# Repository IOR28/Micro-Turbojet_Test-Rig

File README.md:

# Micro-Turbojet Test Rig

This repository contains all the files created during my thesis, Test Rig Design for a Micro-Turbojet Engine. More information about these contents, designs and uses can be found in the document of the thesis.

Different parts of the test rig design where explored during the project, these are sepparated into folders with the same topic. The explanation of this organization and a brief explanation of each subproject can be found below.

### Contents

+ [StructureDesign](#structuredesign): Autodesk Inventor project
	+ Bellmouth: Parts, drawings and final files
	+ CommercialParts
	+ DesignedParts: Parts and drawings
+ [DataAcquisitionMCs](#dataacquisitionmcs): MPLAB X projects
	+ Pressure
	+ Temperature
	+ Thrust_Flow
+ [DataProcessingMaster](#dataprocessingmaster): Python files and classes
+ [PCBDesigns](#pcbdesigns): Autodesk Eagle projects
	+ RTD_conditioning
	+ System_control
	+ General_board

## [StructureDesign](./StructureDesign)

This folder contains the Autodesk Inventor files of the designed bench. the bench features both [commercial parts](./StructureDesign/CommercialParts) and [designed parts](./StructureDesign/DesignedParts). The design of a [bellmouth](./StructureDesign/Bellmouth) is also included.

All the designed components have their corresponding sketches in DWG, DXF and PDF formats so that they can be manufactured. The bellmouth is expected to be 3D printed, therefore, STL files are profided along with the sketches. The links to the commercial parts can be found in the budget of the project (document).

## [DataAcquisitionMCs](./DataAcquisitionMCs)

Here the MPLAB X projects can be found. Files are coded in C and are divided into 3 projects (each one corresponding to a microcontroller):
+ Pressure
+ Temperature
+ Thrust_Flow

In order to program the microcontrollers it is necessary to open the projects in the MPLAB X IDE, compile them and then transfer them to the mCs through a USB cable.

## [DataProcessingMaster](./DataProcessingMaster)

This folder contains the Python files and classes necessary to program the Raspberry Pi 4 that acts as master. This master connects to the microcontrollers in order to gather data and save it to a database.

All the files must be saved into the `Turbojet` folder (as they are organized) inside the Raspberry Pi 4 in order to function properly. More information about how the program works and how to modify it can be found in the document.

## [PCBDesigns](./PCBDesigns)

Three boards are designed to hold all the electronics together. Autodesk Eagle is used to create these and their projects can be found inside this folder. Boards are:
+ An RTD PT100 circuit board
+ A control board
+ A base board to hold all conditioning boards

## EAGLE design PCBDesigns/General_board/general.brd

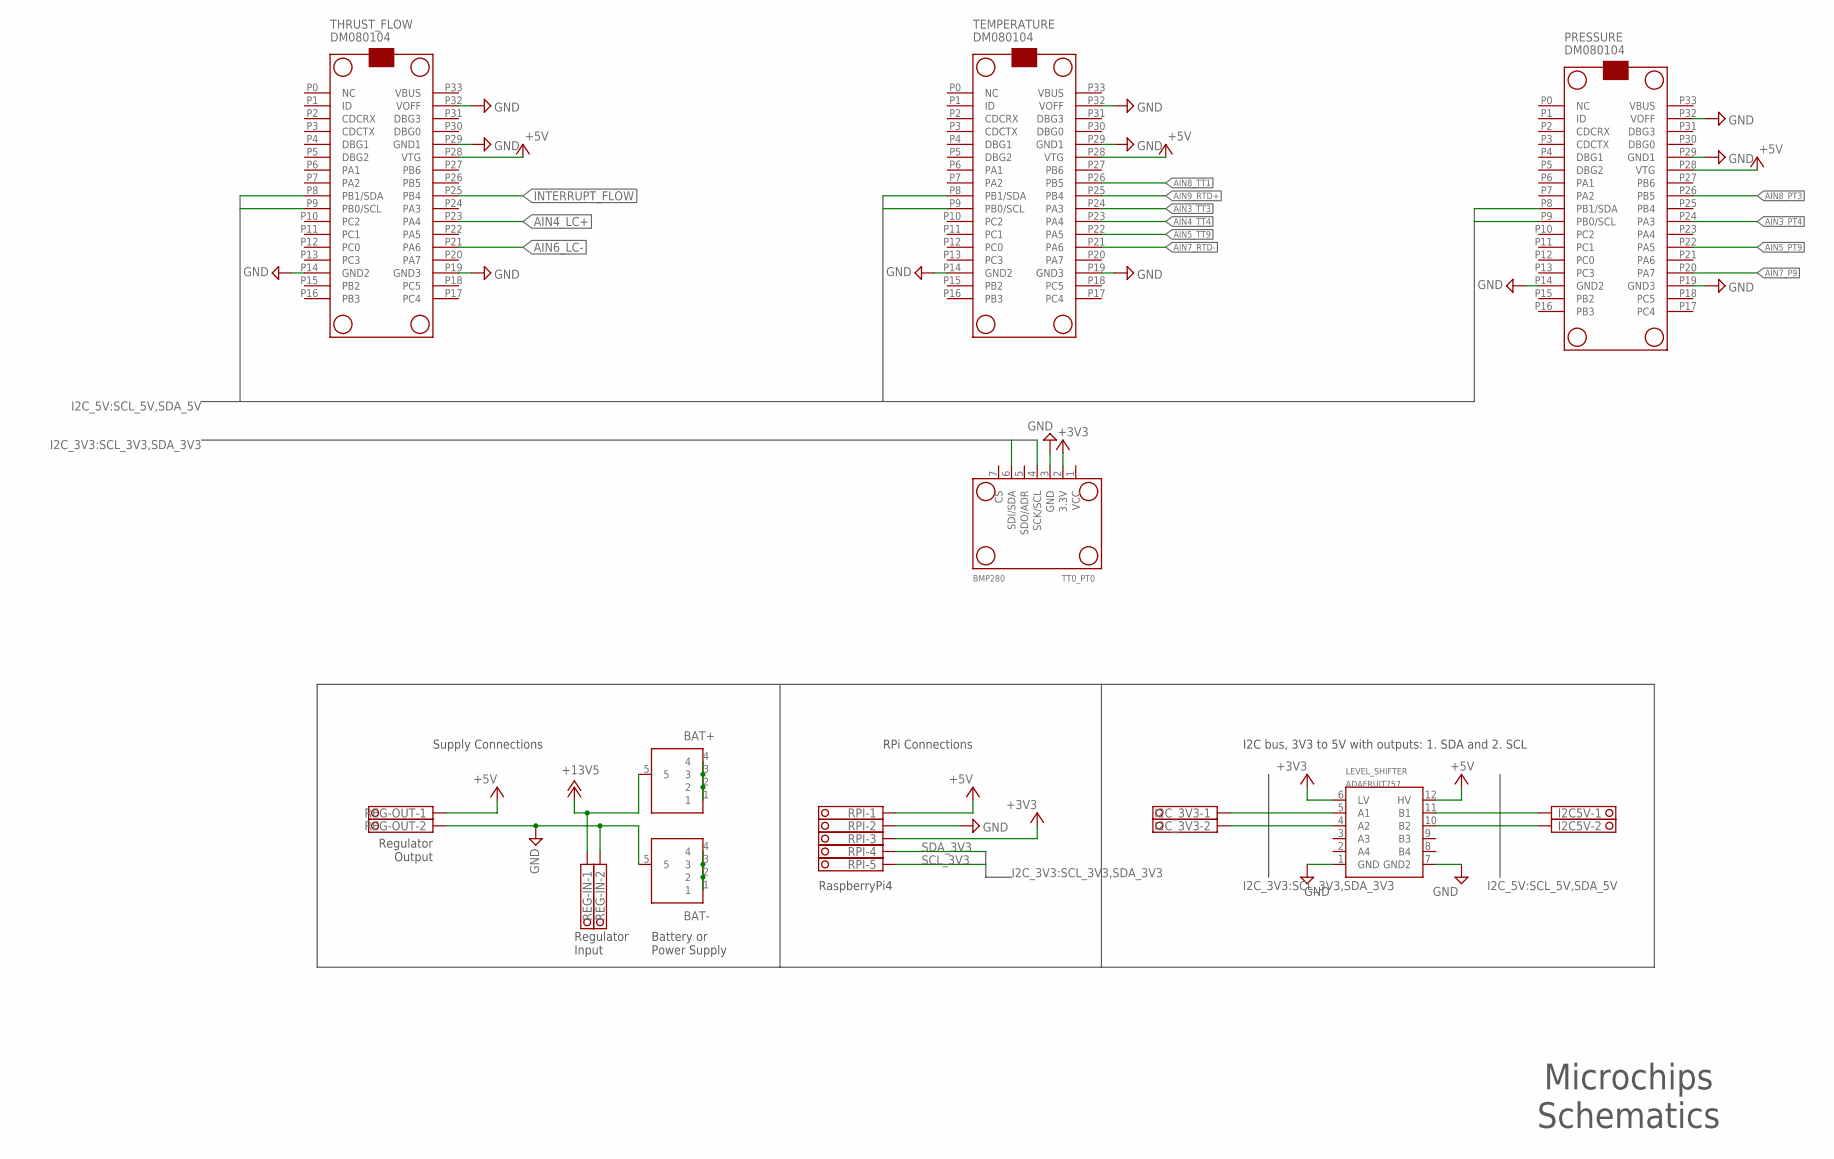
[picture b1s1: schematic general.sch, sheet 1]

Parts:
BAT+: 73099-2730990; 730990
BAT-: 73099-0; 730990
I2C5V, I2C_3V3: 1751248
LEVEL_SHIFTER: ADAFRUIT757
PRESSURE: DM080104
REG-IN: 1751248
REG-OUT: 1751248
RPI: 1751277
TEMPERATURE: DM080104
THRUST_FLOW: DM080104
TT0_PT0: BMP280

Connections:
+3V3: LEVEL_SHIFTER.6 (LV), RPI.3, TT0_PT0.2 (3.3V); also elsewhere on the board
+5V: LEVEL_SHIFTER.12 (HV), PRESSURE.P28 (VTG), REG-OUT.1, RPI.1, TEMPERATURE.P28 (VTG), THRUST_FLOW.P28 (VTG); also elsewhere on the board
+13V5: BAT+.5, REG-IN.1; also elsewhere on the board
AIN3_PT4: PRESSURE.P24 (PA3); also elsewhere on the board
AIN3_TT3: TEMPERATURE.P24 (PA3); also elsewhere on the board
AIN4_LC+: THRUST_FLOW.P23 (PA4); also elsewhere on the board
AIN4_TT4: TEMPERATURE.P23 (PA4); also elsewhere on the board
AIN5_PT9: PRESSURE.P22 (PA5); also elsewhere on the board
AIN5_TT9: TEMPERATURE.P22 (PA5); also elsewhere on the board
AIN6_LC-: THRUST_FLOW.P21 (PA6); also elsewhere on the board
AIN7_P9: PRESSURE.P20 (PA7); also elsewhere on the board
AIN7_RTD-: TEMPERATURE.P21 (PA6); also elsewhere on the board
AIN8_PT3: PRESSURE.P26 (PB5); also elsewhere on the board
AIN8_TT1: TEMPERATURE.P26 (PB5); also elsewhere on the board
AIN9_RTD+: TEMPERATURE.P25 (PB4); also elsewhere on the board
GND: BAT-.5, LEVEL_SHIFTER.1 (GND), LEVEL_SHIFTER.7 (GND2), PRESSURE.P14 (GND2), PRESSURE.P19 (GND3), PRESSURE.P29 (GND1), PRESSURE.P32 (VOFF), REG-IN.2, REG-OUT.2, RPI.2, TEMPERATURE.P14 (GND2), TEMPERATURE.P19 (GND3), TEMPERATURE.P29 (GND1), TEMPERATURE.P32 (VOFF), THRUST_FLOW.P14 (GND2), THRUST_FLOW.P19 (GND3), THRUST_FLOW.P29 (GND1), THRUST_FLOW.P32 (VOFF), TT0_PT0.3 (GND); also elsewhere on the board
INTERRUPT_FLOW: THRUST_FLOW.P25 (PB4); also elsewhere on the board
unnamed: BAT+.1, BAT+.2, BAT+.3, BAT+.4
unnamed: BAT-.1, BAT-.2, BAT-.3, BAT-.4
SCL_3V3: I2C_3V3.2, LEVEL_SHIFTER.4 (A2), RPI.5, TT0_PT0.4 (SCK/SCL); also elsewhere on the board
SCL_5V: I2C5V.2, LEVEL_SHIFTER.10 (B2), PRESSURE.P9 (PB0/SCL), TEMPERATURE.P9 (PB0/SCL), THRUST_FLOW.P9 (PB0/SCL)
SDA_3V3: I2C_3V3.1, LEVEL_SHIFTER.5 (A1), RPI.4, TT0_PT0.6 (SDI/SDA); also elsewhere on the board
SDA_5V: I2C5V.1, LEVEL_SHIFTER.11 (B1), PRESSURE.P8 (PB1/SDA), TEMPERATURE.P8 (PB1/SDA), THRUST_FLOW.P8 (PB1/SDA)

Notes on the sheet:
I2C bus, 3V3 to 5V with outputs: 1. SDA and 2. SCL
Supply Connections
Microchips Schematics
RPi Connections
Regulator Output
Battery or Power Supply
RaspberryPi4
Regulator Input

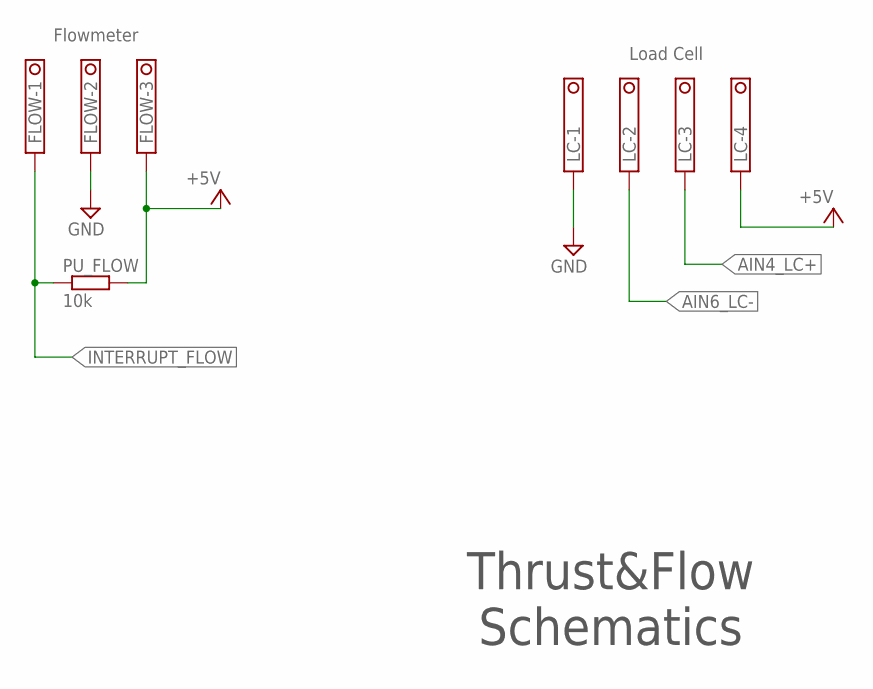
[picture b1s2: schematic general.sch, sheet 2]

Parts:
FLOW: 1751251
LC: 1751264
PU_FLOW: 10k; 0207/10

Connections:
+5V: FLOW.3, LC.4, PU_FLOW.2; also elsewhere on the board
AIN4_LC+: LC.3; also elsewhere on the board
AIN6_LC-: LC.2; also elsewhere on the board
GND: FLOW.2, LC.1; also elsewhere on the board
INTERRUPT_FLOW: FLOW.1, PU_FLOW.1; also elsewhere on the board

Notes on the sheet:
Thrust&Flow Schematics
Flowmeter
Load Cell

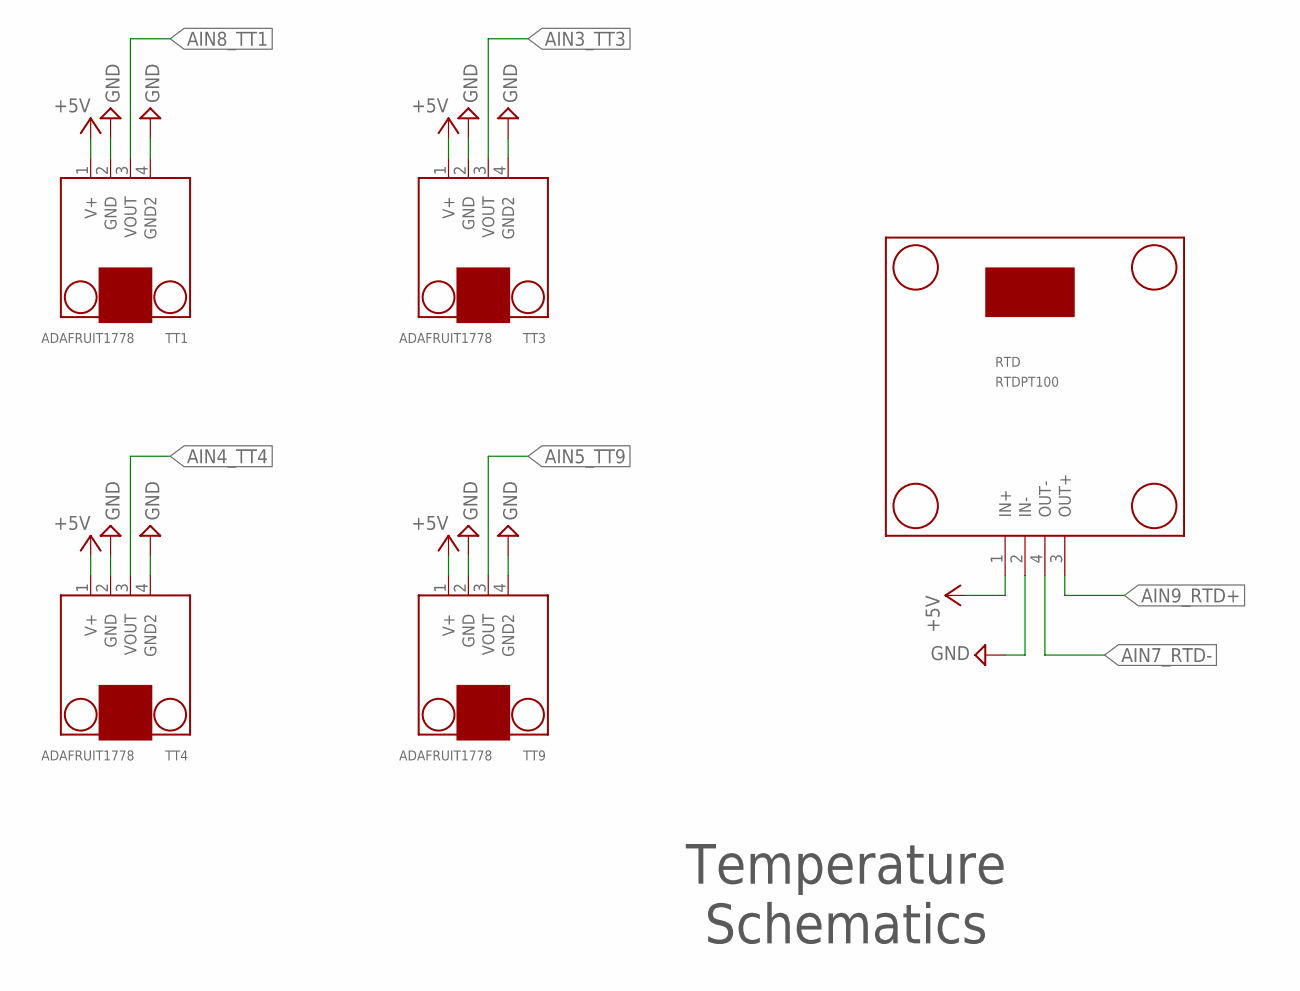
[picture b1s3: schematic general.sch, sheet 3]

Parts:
RTD: RTDPT100
TT1, TT3, TT4, TT9: ADAFRUIT1778

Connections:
+5V: RTD.1 (IN+), TT1.1 (V+), TT3.1 (V+), TT4.1 (V+), TT9.1 (V+); also elsewhere on the board
AIN3_TT3: TT3.3 (VOUT); also elsewhere on the board
AIN4_TT4: TT4.3 (VOUT); also elsewhere on the board
AIN5_TT9: TT9.3 (VOUT); also elsewhere on the board
AIN7_RTD-: RTD.4 (OUT-); also elsewhere on the board
AIN8_TT1: TT1.3 (VOUT); also elsewhere on the board
AIN9_RTD+: RTD.3 (OUT+); also elsewhere on the board
GND: RTD.2 (IN-), TT1.2 (GND), TT1.4 (GND2), TT3.2 (GND), TT3.4 (GND2), TT4.2 (GND), TT4.4 (GND2), TT9.2 (GND), TT9.4 (GND2); also elsewhere on the board

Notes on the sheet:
Temperature Schematics

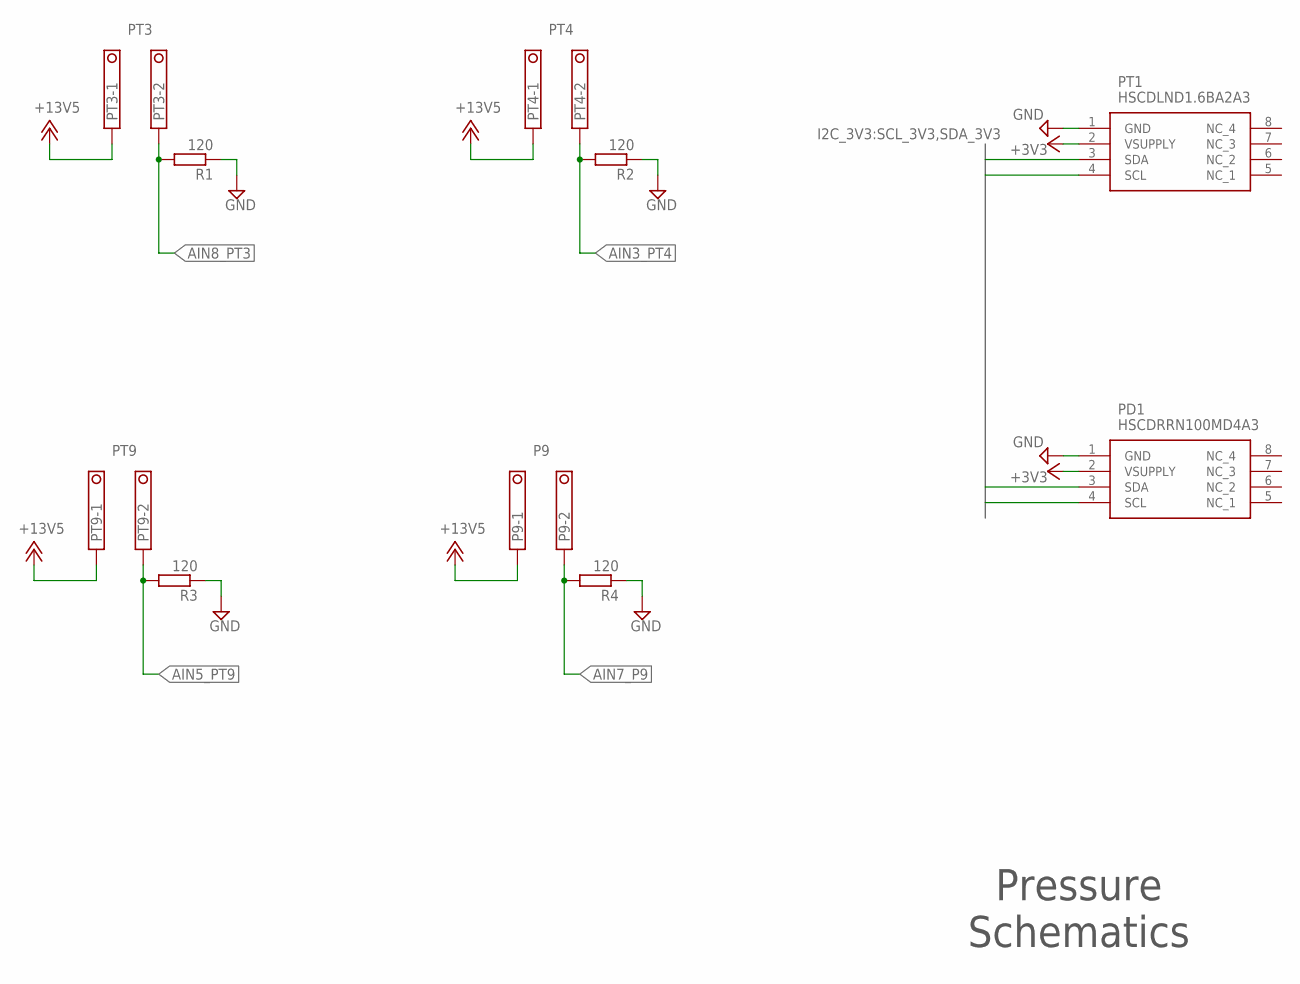
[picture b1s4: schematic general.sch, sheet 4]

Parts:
P9: 1751248
PD1: HSCDRRN100MD4A3
PT1: HSCDLND1.6BA2A3
PT3, PT4, PT9: 1751248
R1, R2, R3, R4: 120; 0207/10

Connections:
+3V3: PD1.2 (VSUPPLY), PT1.2 (VSUPPLY); also elsewhere on the board
+13V5: P9.1, PT3.1, PT4.1, PT9.1; also elsewhere on the board
AIN3_PT4: PT4.2, R2.2; also elsewhere on the board
AIN5_PT9: PT9.2, R3.2; also elsewhere on the board
AIN7_P9: P9.2, R4.2; also elsewhere on the board
AIN8_PT3: PT3.2, R1.2; also elsewhere on the board
GND: PD1.1 (GND), PT1.1 (GND), R1.1, R2.1, R3.1, R4.1; also elsewhere on the board
SCL_3V3: PD1.4 (SCL), PT1.4 (SCL); also elsewhere on the board
SDA_3V3: PD1.3 (SDA), PT1.3 (SDA); also elsewhere on the board

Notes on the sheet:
Pressure Schematics
PT3
PT4
PT9

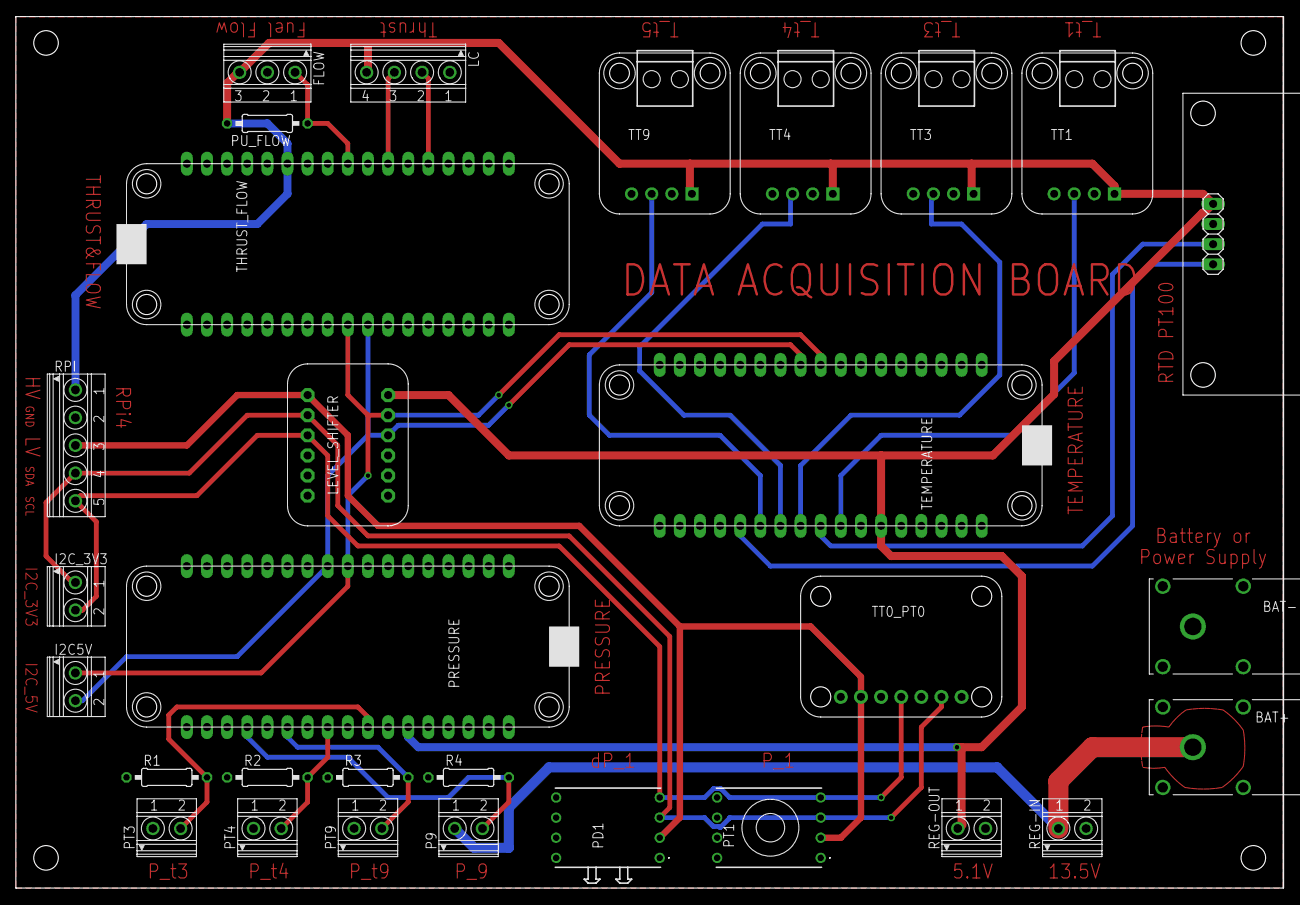
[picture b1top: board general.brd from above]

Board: 2 copper layers, 159.9 x 110.0 mm, 30 parts (0 on the bottom side), 23 nets.

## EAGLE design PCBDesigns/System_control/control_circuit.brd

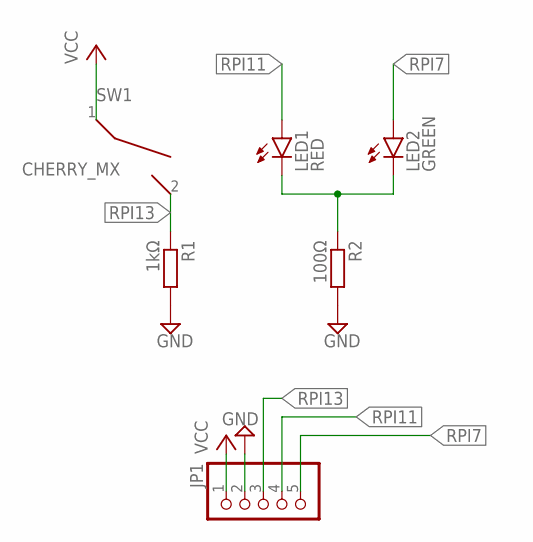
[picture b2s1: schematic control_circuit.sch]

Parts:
JP1: PINHD-1X5; 1X05
LED1: RED; LED5MM
LED2: GREEN; LED5MM
R1: 1kΩ; 0207/10
R2: 100Ω; 0207/10
SW1: CHERRY_MX; MX1A-XXNN

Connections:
GND: JP1.2, R1.2, R2.2
unnamed: LED1.K (C), LED2.K (C), R2.1
RPI7: JP1.5, LED2.A
RPI11: JP1.4, LED1.A
RPI13: JP1.3, R1.1, SW1.2
VCC: JP1.1, SW1.1

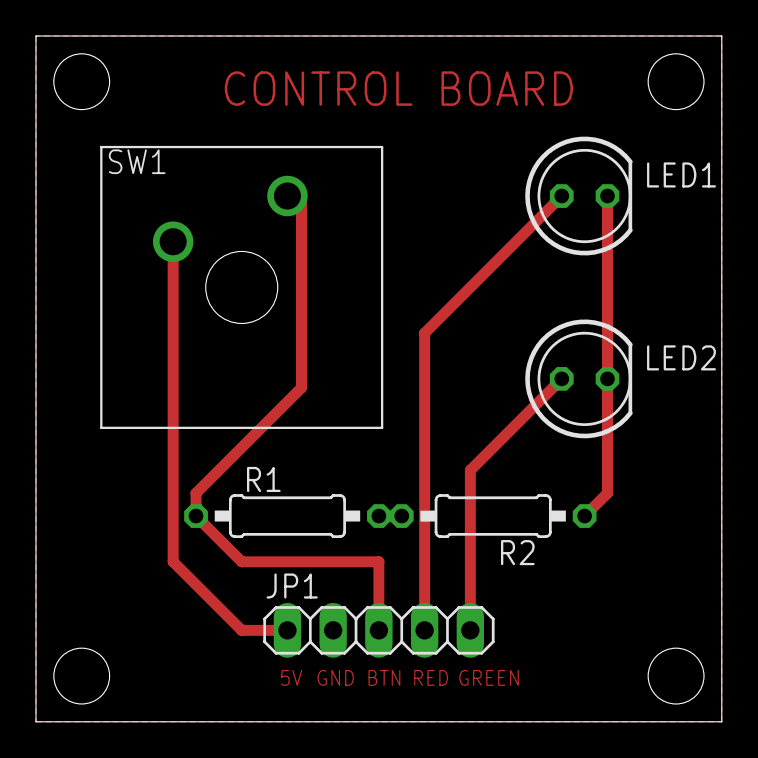
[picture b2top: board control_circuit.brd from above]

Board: 2 copper layers, 38.1 x 38.1 mm, 6 parts (0 on the bottom side), 6 nets.

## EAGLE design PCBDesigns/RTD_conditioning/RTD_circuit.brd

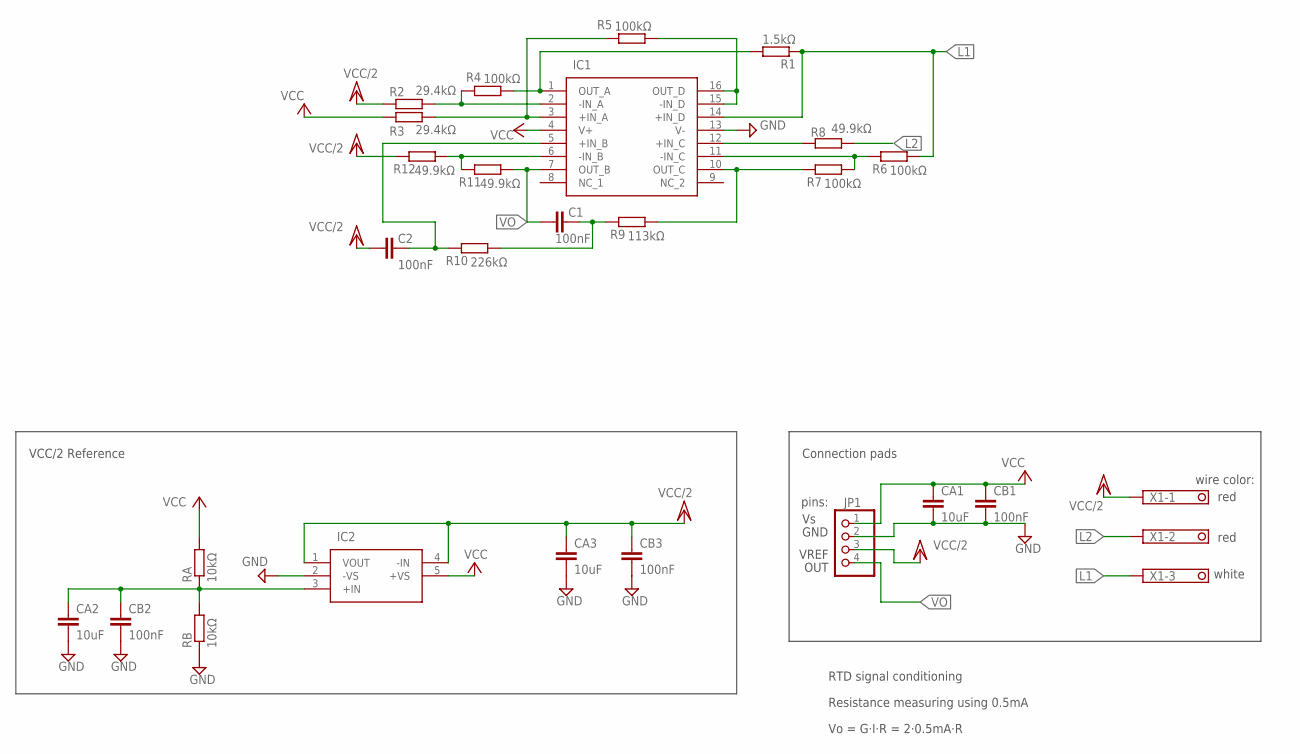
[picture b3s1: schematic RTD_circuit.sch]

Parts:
C1, C2: 100nF; C0603
CA1, CA2, CA3: 10uF; C0603
CB1, CB2, CB3: 100nF; C0603
IC1: LT1079SW#PBF; SOIC127P1032X264-16N
IC2: AD8031ARTZ-R2; SOT95P280X145-5N
JP1: PINHD-1X4; 1X04
R1: 1.5kΩ; R0603
R2, R3: 29.4kΩ; R0603
R4, R5, R6, R7: 100kΩ; R0603
R8, R11, R12: 49.9kΩ; R0603
R9: 113kΩ; R0603
R10: 226kΩ; R0603
RA: 10kΩ; R0603
RB: 10kΩ; R0603
X1: 1751251

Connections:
DIVIDER: CA2.1, CB2.1, IC2.3 (+IN), RA.1, RB.2
GND: CA1.2, CA2.2, CA3.2, CB1.2, CB2.2, CB3.2, IC1.13 (V-), IC2.2 (-VS), JP1.2, RB.1
L1: IC1.14 (+IN_D), R1.1, R6.1, X1.3
L2: R8.1, X1.2
unnamed: IC1.12 (+IN_C), R8.2
unnamed: IC1.6 (-IN_B), R11.2, R12.1
unnamed: IC1.3 (+IN_A), R3.2, R5.2
unnamed: IC1.2 (-IN_A), R2.2, R4.2
unnamed: IC1.1 (OUT_A), R1.2, R4.1
unnamed: IC1.11 (-IN_C), R6.2, R7.1
unnamed: IC1.15 (-IN_D), IC1.16 (OUT_D), R5.1
unnamed: IC1.10 (OUT_C), R7.2, R9.1
unnamed: C1.1, R9.2, R10.1
unnamed: C2.1, IC1.5 (+IN_B), R10.2
VCC: CA1.1, CB1.1, IC1.4 (V+), IC2.5 (+VS), JP1.1, R3.1, RA.2
VCC/2: C2.2, CA3.1, CB3.1, IC2.1 (VOUT), IC2.4 (-IN), JP1.3, R2.1, R12.2, X1.1
VO: C1.2, IC1.7 (OUT_B), JP1.4, R11.1

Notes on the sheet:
RTD signal conditioning
Resistance measuring using 0.5mA
Vo = G·I·R = 2·0.5mA·R
VCC/2 Reference
wire color:
red
white
Connection pads
pins:
GND
VREF
OUT

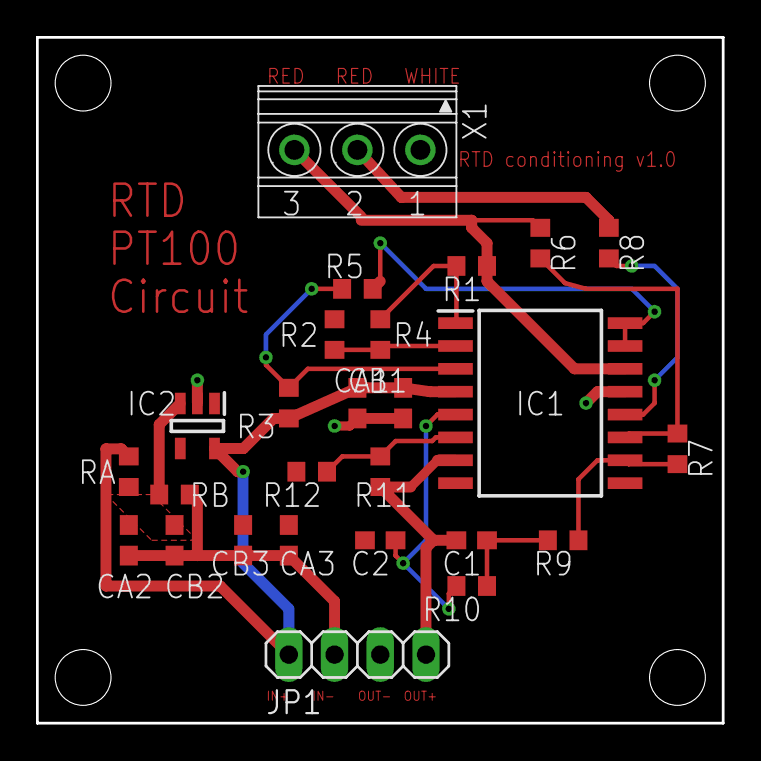
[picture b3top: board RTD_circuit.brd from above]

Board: 2 copper layers, 38.1 x 38.1 mm, 26 parts (0 on the bottom side), 17 nets.

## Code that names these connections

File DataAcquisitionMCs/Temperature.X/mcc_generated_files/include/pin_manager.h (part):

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#include <avr/io.h>
#include "port.h"

//get/set PA4 aliases
#define PA4_SetHigh() do { PORTA_OUTSET = 0x10; } while(0)
#define PA4_SetLow() do { PORTA_OUTCLR = 0x10; } while(0)
#define PA4_Toggle() do { PORTA_OUTTGL = 0x10; } while(0)
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#define PA4_DisableDigitalInputBuffer() do { PORTA.PIN4CTRL = (PORTA.PIN4CTRL & ~PORT_ISC_gm) | 0x4 ; } while(0)
#define PA4_EnableInterruptForLowLevelSensing() do { PORTA.PIN4CTRL = (PORTA.PIN4CTRL & ~PORT_ISC_gm) | 0x5 ; } while(0)

//get/set PB5 aliases
#define PB5_SetHigh() do { PORTB_OUTSET = 0x20; } while(0)
#define PB5_SetLow() do { PORTB_OUTCLR = 0x20; } while(0)
#define PB5_Toggle() do { PORTB_OUTTGL = 0x20; } while(0)
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#define PB5_DisableDigitalInputBuffer() do { PORTB.PIN5CTRL = (PORTB.PIN5CTRL & ~PORT_ISC_gm) | 0x4 ; } while(0)
#define PB5_EnableInterruptForLowLevelSensing() do { PORTB.PIN5CTRL = (PORTB.PIN5CTRL & ~PORT_ISC_gm) | 0x5 ; } while(0)

//get/set PA3 aliases
#define PA3_SetHigh() do { PORTA_OUTSET = 0x8; } while(0)
#define PA3_SetLow() do { PORTA_OUTCLR = 0x8; } while(0)
#define PA3_Toggle() do { PORTA_OUTTGL = 0x8; } while(0)
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#define PA3_DisableDigitalInputBuffer() do { PORTA.PIN3CTRL = (PORTA.PIN3CTRL & ~PORT_ISC_gm) | 0x4 ; } while(0)
#define PA3_EnableInterruptForLowLevelSensing() do { PORTA.PIN3CTRL = (PORTA.PIN3CTRL & ~PORT_ISC_gm) | 0x5 ; } while(0)

//get/set PB4 aliases
#define PB4_SetHigh() do { PORTB_OUTSET = 0x10; } while(0)
#define PB4_SetLow() do { PORTB_OUTCLR = 0x10; } while(0)
#define PB4_Toggle() do { PORTB_OUTTGL = 0x10; } while(0)
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#define PB4_DisableDigitalInputBuffer() do { PORTB.PIN4CTRL = (PORTB.PIN4CTRL & ~PORT_ISC_gm) | 0x4 ; } while(0)
#define PB4_EnableInterruptForLowLevelSensing() do { PORTB.PIN4CTRL = (PORTB.PIN4CTRL & ~PORT_ISC_gm) | 0x5 ; } while(0)

//get/set PA6 aliases
#define PA6_SetHigh() do { PORTA_OUTSET = 0x40; } while(0)
#define PA6_SetLow() do { PORTA_OUTCLR = 0x40; } while(0)
#define PA6_Toggle() do { PORTA_OUTTGL = 0x40; } while(0)
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#define PA6_DisableDigitalInputBuffer() do { PORTA.PIN6CTRL = (PORTA.PIN6CTRL & ~PORT_ISC_gm) | 0x4 ; } while(0)
#define PA6_EnableInterruptForLowLevelSensing() do { PORTA.PIN6CTRL = (PORTA.PIN6CTRL & ~PORT_ISC_gm) | 0x5 ; } while(0)

//get/set PA5 aliases
#define PA5_SetHigh() do { PORTA_OUTSET = 0x20; } while(0)
#define PA5_SetLow() do { PORTA_OUTCLR = 0x20; } while(0)
#define PA5_Toggle() do { PORTA_OUTTGL = 0x20; } while(0)
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#define PA5_DisableDigitalInputBuffer() do { PORTA.PIN5CTRL = (PORTA.PIN5CTRL & ~PORT_ISC_gm) | 0x4 ; } while(0)
#define PA5_EnableInterruptForLowLevelSensing() do { PORTA.PIN5CTRL = (PORTA.PIN5CTRL & ~PORT_ISC_gm) | 0x5 ; } while(0)

//get/set PB1 aliases
#define PB1_SetHigh() do { PORTB_OUTSET = 0x2; } while(0)
#define PB1_SetLow() do { PORTB_OUTCLR = 0x2; } while(0)
#define PB1_Toggle() do { PORTB_OUTTGL = 0x2; } while(0)
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#define PB1_DisableDigitalInputBuffer() do { PORTB.PIN1CTRL = (PORTB.PIN1CTRL & ~PORT_ISC_gm) | 0x4 ; } while(0)
#define PB1_EnableInterruptForLowLevelSensing() do { PORTB.PIN1CTRL = (PORTB.PIN1CTRL & ~PORT_ISC_gm) | 0x5 ; } while(0)

//get/set PB0 aliases
#define PB0_SetHigh() do { PORTB_OUTSET = 0x1; } while(0)
#define PB0_SetLow() do { PORTB_OUTCLR = 0x1; } while(0)
#define PB0_Toggle() do { PORTB_OUTTGL = 0x1; } while(0)
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
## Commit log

2021-08-21 Structure files
    Added all the files that simulate the test rig structure, included designed parts with drawings.
2021-08-21 Added MPLAB X files
    MPLAB X IDE files to program the data acquisition micro-controllers (3x ATtiny1627).
2021-08-21 Added master files
    Code files to program a Raspberry Pi 4 as master of the data acquisition system.
2021-08-21 Added PCB designs
    Schematics and board designs of the whole electronic system.
2021-08-26 Name change (Union to Mounting)
    Change from:
    Engine_Union to Engine_Mounting
    Union_axis to Mounting_Shaft
    Files:
    Assembly (relationships)
    Part names
2021-10-27 Bug solved, database saves.
2021-10-27 deleted test files

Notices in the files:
DataAcquisitionMCs/Temperature.X/mcc_generated_files/include/pin_manager.h:
(c) 2018 Microchip Technology Inc. and its subsidiaries.
